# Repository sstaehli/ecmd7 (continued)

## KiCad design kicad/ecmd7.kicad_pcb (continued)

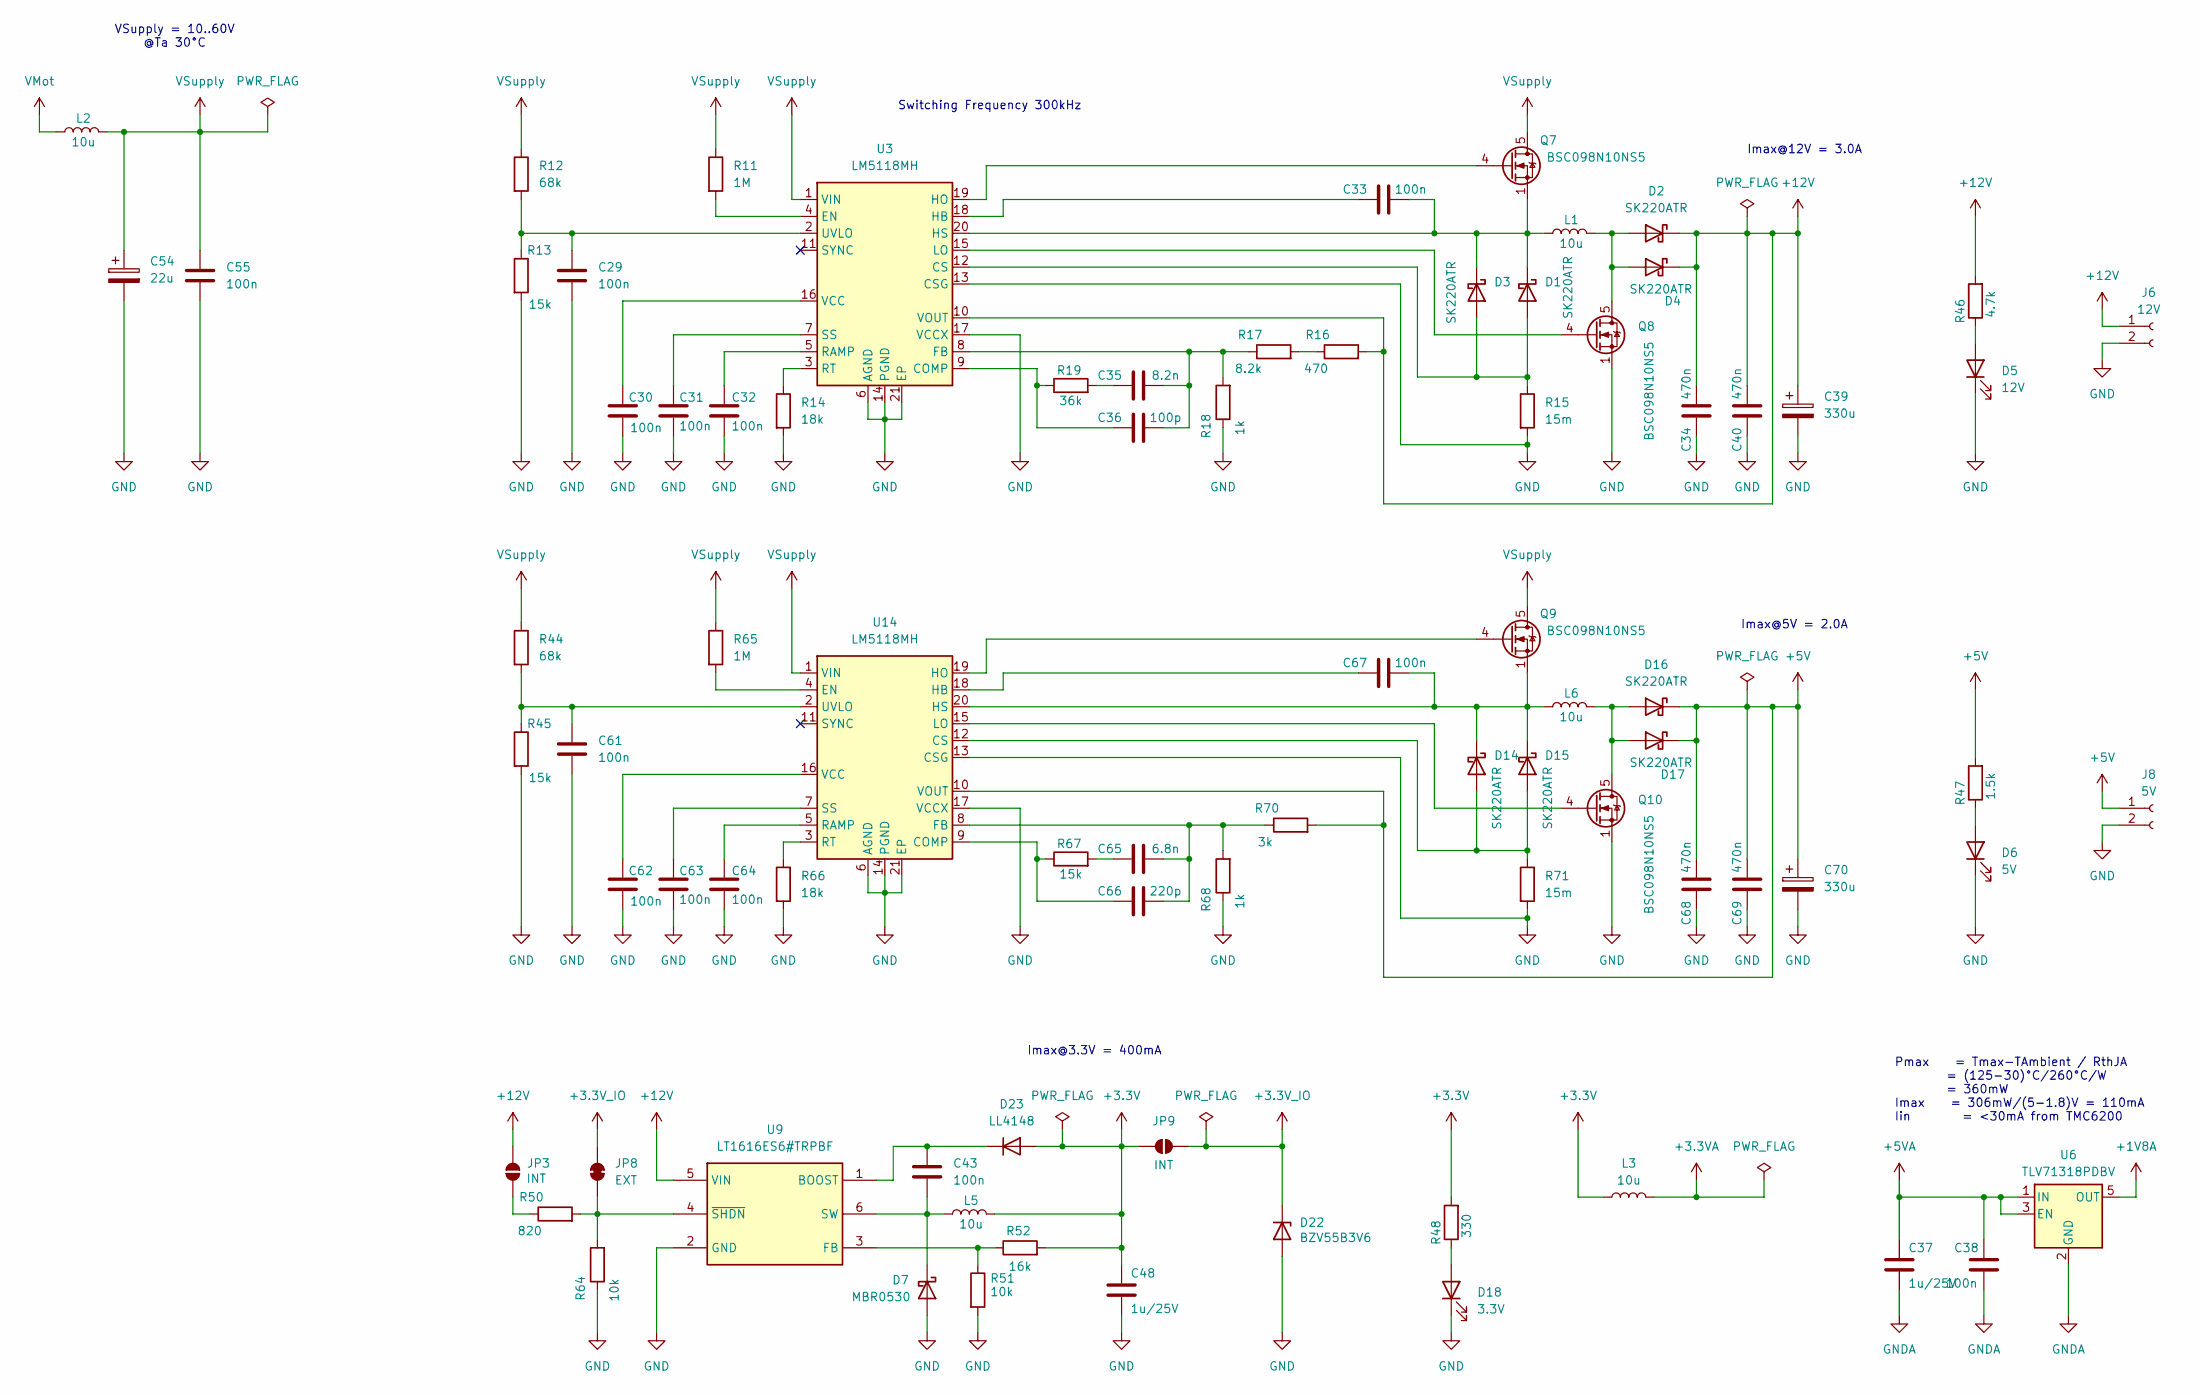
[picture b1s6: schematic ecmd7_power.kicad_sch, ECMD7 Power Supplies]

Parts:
C29, C30, C31, C32, C33, C38, C43, C55, C61, C62, C63, C64, C67: 100n; C_0805_2012Metric
C34, C40, C68, C69: 470n; C_0805_2012Metric
C35: 8.2n; C_0805_2012Metric
C36: 100p; C_0805_2012Metric
C37, C48: 1u/25V; C_0805_2012Metric
C39, C70: 330u; CP_Elec_6.3x9.9
C54: 22u; CP_Elec_6.3x9.9
C65: 6.8n; C_0805_2012Metric
C66: 220p; C_0805_2012Metric
D1, D2, D3, D4, D14, D15, D16, D17: SK220ATR; D_SMA
D5: 12V; D_0805_2012Metric
D6: 5V; D_0805_2012Metric
D7: MBR0530; D_SOD-123
D18: 3.3V; D_0805_2012Metric
D22: BZV55B3V6; D_MiniMELF
D23: LL4148; D_MiniMELF
J6: 12V; PinSocket_1x02_P2.54mm_Vertical
J8: 5V; PinSocket_1x02_P2.54mm_Vertical
JP3, JP9: INT; SolderJumper-2_P1.3mm_Open_RoundedPad1.0x1.5mm
JP8: EXT; SolderJumper-2_P1.3mm_Open_RoundedPad1.0x1.5mm
L1, L2, L5, L6: 10u; L_TechFuse_SL0530; Mouser Part Number 851-0530CDMCCDS100MC
L3: 10u; L_0805_2012Metric
Q7, Q8, Q9, Q10: BSC098N10NS5; TDSON-8-1
R11, R65: 1M; R_0805_2012Metric
R12, R44: 68k; R_0805_2012Metric
R13, R45, R67: 15k; R_0805_2012Metric
R14, R66: 18k; R_0805_2012Metric
R15, R71: 15m; R_0612_1632Metric
R16: 470; R_0805_2012Metric
R17: 8.2k; R_0805_2012Metric
R18, R68: 1k; R_0805_2012Metric
R19: 36k; R_0805_2012Metric
R46: 4.7k; R_0805_2012Metric
R47: 1.5k; R_0805_2012Metric
R48: 330; R_0805_2012Metric
R50: 820; R_0805_2012Metric
R51, R64: 10k; R_0805_2012Metric
R52: 16k; R_0805_2012Metric
R70: 3k; R_0805_2012Metric
U3, U14: LM5118MH; Texas_PWP0020A
U6: TLV71318PDBV; SOT-23-5
U9: LT1616ES6#TRPBF; SOT-23-6; Mouser Part Number 584-LT1616ES6#TRPBF

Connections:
+1V8A: U6.5 (OUT); also elsewhere on the board
+3.3V: C48.1, D23.2 (A), JP9.1 (A), L3.1, L5.2, R48.2, R52.2; also elsewhere on the board
+3.3VA: L3.2; also elsewhere on the board
+3.3V_IO: D22.1 (K), JP8.2 (B), JP9.2 (B); also elsewhere on the board
+5V: C68.2, C69.2, C70.1, D16.1 (K), D17.1 (K), J8.1, R47.2, R70.2, U14.10 (VOUT); also elsewhere on the board
+5VA: C37.1, C38.1, U6.1 (IN), U6.3 (EN); also elsewhere on the board
+12V: C34.2, C39.1, C40.2, D2.1 (K), D4.1 (K), J6.1, JP3.1 (A), R16.2, R46.2, U3.10 (VOUT), U9.5 (VIN); also elsewhere on the board
GND: C29.2, C30.2, C31.2, C32.2, C34.1, C39.2, C40.1, C48.2, C54.2, C55.2, C61.2, C62.2, C63.2, C64.2, C68.1, C69.1, C70.2, D5.1 (K), D6.1 (K), D7.2 (A), D18.1 (K), D22.2 (A), J6.2, J8.2, Q8.1 (S), Q8.2 (S), Q8.3 (S), Q10.1 (S), Q10.2 (S), Q10.3 (S), R13.2, R14.2, R15.2, R18.1, R45.2, R51.2, R64.1, R66.2, R68.1, R71.2, U3.6 (AGND), U3.13 (CSG), U3.14 (PGND), U3.17 (VCCX), U3.21 (EP), U9.2 (GND), U14.6 (AGND), U14.13 (CSG), U14.14 (PGND), U14.17 (VCCX), U14.21 (EP); also elsewhere on the board
GNDA: C37.2, C38.2, U6.2 (GND); also elsewhere on the board
unnamed: C35.1, R19.2
unnamed: C65.1, R67.2
unnamed: D1.2 (A), D3.2 (A), R15.1, U3.12 (CS)
unnamed: C33.2, D1.1 (K), D3.1 (K), L1.1, Q7.1 (S), Q7.2 (S), Q7.3 (S), U3.20 (HS)
unnamed: D2.2 (A), D4.2 (A), L1.2, Q8.5 (D)
unnamed: D5.2 (A), R46.1
unnamed: D6.2 (A), R47.1
unnamed: C43.2, D7.1 (K), L5.1, U9.6 (SW)
unnamed: D14.2 (A), D15.2 (A), R71.1, U14.12 (CS)
unnamed: C67.2, D14.1 (K), D15.1 (K), L6.1, Q9.1 (S), Q9.2 (S), Q9.3 (S), U14.20 (HS)
unnamed: D16.2 (A), D17.2 (A), L6.2, Q10.5 (D)
unnamed: D18.2 (A), R48.1
unnamed: C43.1, D23.1 (K), U9.1 (BOOST)
unnamed: JP3.2 (B), R50.1
unnamed: JP8.1 (A), R50.2, R64.2, U9.4 (~SHDN)
unnamed: Q7.4 (G), U3.19 (HO)
unnamed: Q8.4 (G), U3.15 (LO)
unnamed: Q9.4 (G), U14.19 (HO)
unnamed: Q10.4 (G), U14.15 (LO)
unnamed: R16.1, R17.2
unnamed: C36.1, R19.1, U3.9 (COMP)
unnamed: R11.2, U3.4 (EN)
unnamed: C35.2, C36.2, R17.1, R18.2, U3.8 (FB)
unnamed: C33.1, U3.18 (HB)
unnamed: C32.1, U3.5 (RAMP)
unnamed: R14.1, U3.3 (RT)
unnamed: C31.1, U3.7 (SS)
unnamed: C29.1, R12.2, R13.1, U3.2 (UVLO)
unnamed: C30.1, U3.16 (VCC)
unnamed: R51.1, R52.1, U9.3 (FB)
unnamed: C66.1, R67.1, U14.9 (COMP)
unnamed: R65.2, U14.4 (EN)
unnamed: C65.2, C66.2, R68.2, R70.1, U14.8 (FB)
unnamed: C67.1, U14.18 (HB)
unnamed: C64.1, U14.5 (RAMP)
unnamed: R66.1, U14.3 (RT)
unnamed: C63.1, U14.7 (SS)
unnamed: C61.1, R44.2, R45.1, U14.2 (UVLO)
unnamed: C62.1, U14.16 (VCC)
VMot: L2.1; also elsewhere on the board
VSupply: C54.1, C55.1, L2.2, Q7.5 (D), Q9.5 (D), R11.1, R12.1, R44.1, R65.1, U3.1 (VIN), U14.1 (VIN)

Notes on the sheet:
Imax@3.3V = 400mA
Imax@5V = 2.0A
Switching Frequency 300kHz
Imax@12V = 3.0A
Pmax = Tmax-TAmbient / RthJA = (125-30)°C/260°C/W = 360mW Imax = 306mW/(5-1.8)V = 110mA Iin = <30mA from TMC6200
VSupply = 10..60V @Ta 30°C

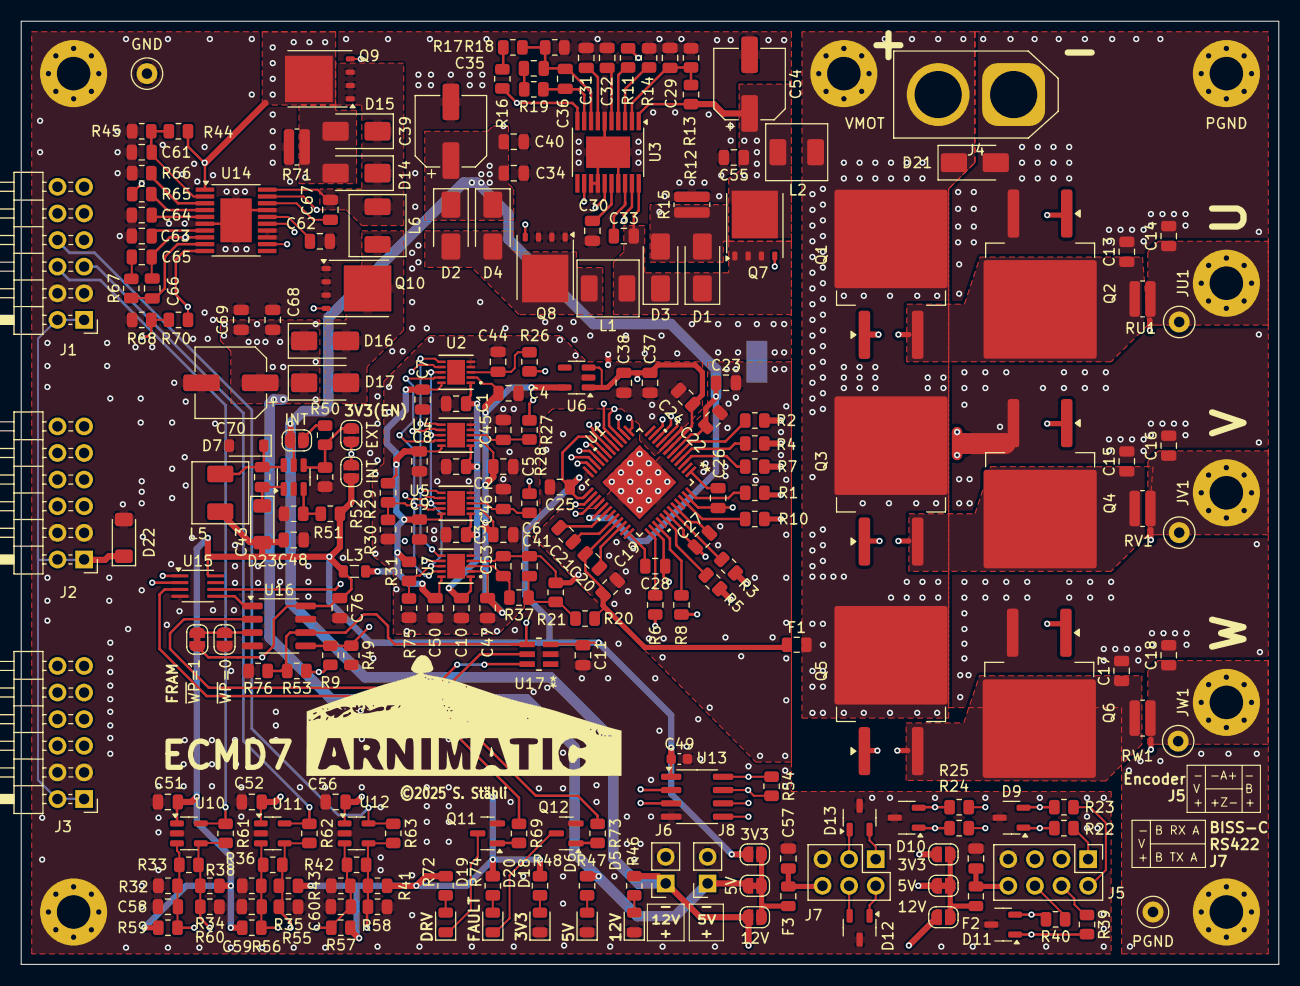
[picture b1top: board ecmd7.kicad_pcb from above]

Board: 4 copper layers, 120.0 x 90.0 mm, 250 parts (1 on the bottom side), 150 nets.

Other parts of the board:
Logo: LOGO

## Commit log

2025-09-22 User requirements
2025-09-22 Edit README.md
2025-09-22 Update diagram
2025-09-27 WIP: Add PCB
2025-09-27 WIP: Add supply
2025-09-27 WIP: Add ADC inputs
2025-09-29 WIP: Update ADC schematic with cheaper solution
2025-10-01 WIP: Add sensor interface Re-partition schematic
2025-10-08 Finlize schematics
2025-10-23 Finalize schematic Add ESD protection Align connector pinout with Arty A7 and Zybo Z7 PMOD
2025-10-23 PCB dimension and initial placement
2025-10-24 Initial component placement
2025-10-28 WIP: Update symbols, fix ERC errors
2025-10-28 Update README/user requirements
2025-10-28 WIP: Power stage and ADC routing
2025-10-31 WIP: Partial routing
2025-10-31 WIP: advnced routing
2025-11-02 Routing complete, DRC successful
2025-11-02 Final layout
2025-11-02 Ordered layout
2025-11-07 Update project structure for enhancment with firmware and software
2025-11-07 CI: Update KiCad image tag
2025-11-07 CI: Remove make command
2025-11-07 CI: Fix paths and variable resolution
2025-11-07 Fix path
2025-11-07 CI: Fix pages job name
2025-11-07 Remove requirements from main README.d
2025-11-07 Fix hugo config
2025-11-07 Minimal doc output example
2025-11-07 Fix base URL
2025-11-07 Add debug for pages URL
2025-11-07 Try relative path
2025-11-07 WIP: Update layout
2025-11-07 Update pages to support latex and mermaid
2025-11-07 WIP: Add interface documentation
2025-11-07 Fix typo
2025-11-07 CI: Change KiCad image for 3D models
2025-11-10 WIP: Update documentation
2025-11-10 Cleanup schematic
2025-11-10 Fix download links
2025-11-12 Cleanup schematic, add busses
2025-12-10 WIP: Add power pole simulation
2025-12-10 General schematic cleanup
2025-12-12 Fix MOSI/MISO naming ADC
2025-12-12 Fix power connector polarity
2026-01-08 Add github workflow
2026-01-08 Refactor CI workflow to use new build job
2026-01-08 Fix env variable substitution
2026-01-08 Fix CI job permissions
2026-01-08 CI: Separate Hugo build and deploy stages
2026-01-08 CI: Update pages action version
2026-01-08 Update URL setting for hugo
2026-01-09 Try fixing base URL with dash
2026-01-09 hugo: Add relURL attributes (for github pages)
2026-01-09 CI: Update hugo action version
2026-01-09 Fix base URL again for Github
2026-01-09 Update README.md with links to GitLab and GitHub
2026-01-09 Update Makefile for Linux use
2026-01-09 Add links to GitLab and GitHub repositories
2026-01-09 Doc: Add picture of first protoype
2026-01-09 Update circuit description
2026-01-12 Update workflow with Gerber generation and package release
2026-01-12 Fix kicad job
2026-01-12 Add license file
2026-01-12 Add pipeline status batches to README
